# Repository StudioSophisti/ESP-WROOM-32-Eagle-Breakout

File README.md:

# ESP-WROOM-32-Eagle-Breakout
A breadboard compatible Eagle breakout board for Espressif's ESP32 module ESP-WROOM-32. The ESP32 is a powerful and low-cost Wifi/Bluetooth chip that enables great Internet-Of-Things applications. Studio Sophisti is using this chip in several projects, including a work-in-progress redesign of Ping (http://www.studiosophisti.nl/ping)

The ESP-WROOM-32 can be purchased directly from Espressif or from a distributor like Adafruit: https://www.adafruit.com/product/3320

The board contains reverse-voltage protections, 2 buttons (1 for reset and 1 for activating programming mode), and a diode on the RX line so the IC is 5V serial port compatible.

Power it from a 3.0-3.3V power source.

The design has been tested and works.

### Partlist

- 2 SPST switches: Farnell 2468741
- 2 10k resistors: Farnell 2130939
- 1 10uF capacitor: Farnell 2494230
- 1 1N4148 diode: Farnell 1466524
- 1 2N2007E mosfet: Farnell 2317616

### PCB Preview

Generated with GerberTools from ThisIsNotRocketScience (https://github.com/ThisIsNotRocketScience/GerberTools), thanks Stijn!

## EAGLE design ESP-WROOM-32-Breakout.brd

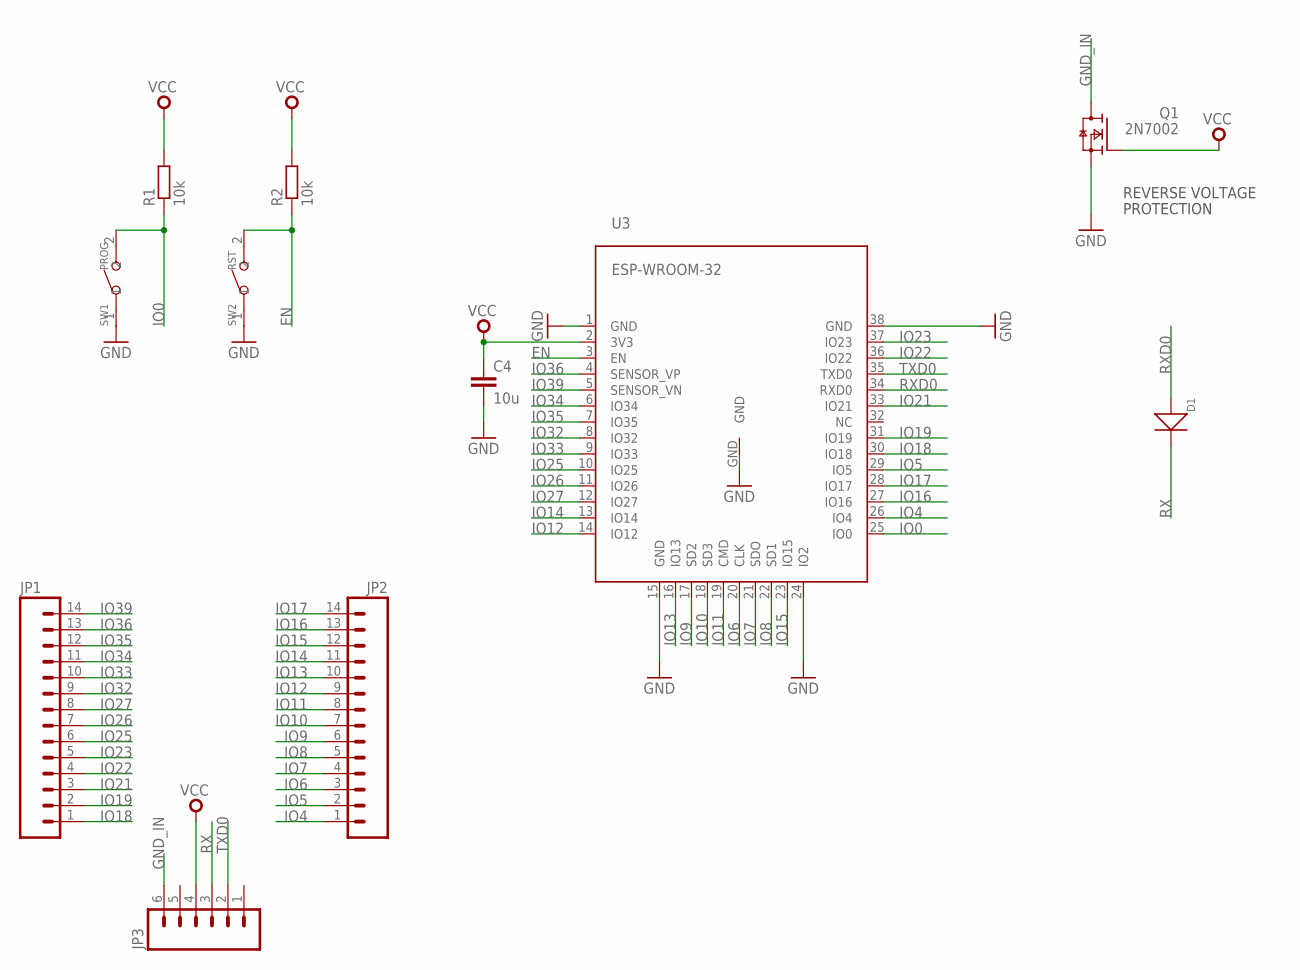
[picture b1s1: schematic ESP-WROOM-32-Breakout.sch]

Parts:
C4: 10u; C0603
D1: DIODE'0805'; SOD-323
JP1, JP2: M14; 1X14
JP3: M06SILK_FEMALE_PTH; 1X06
Q1: 2N7002; SOT23
R1, R2: 10k; R0603
SW1: PROG; SW2-4.0-6.0X3.0X2.5MM
SW2: RST; SW2-4.0-6.0X3.0X2.5MM
U3: ESP-WROOM-32

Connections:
EN: R2.1, SW2.2, U3.3 (EN)
GND: C4.2, Q1.2 (S), SW1.1, SW2.1, U3.1 (GND), U3.15 (GND), U3.24 (IO2), U3.38 (GND), U3.GND
GND_IN: JP3.6, Q1.3 (D)
IO0: R1.1, SW1.2, U3.25 (IO0)
IO4: JP2.1, U3.26 (IO4)
IO5: JP2.2, U3.29 (IO5)
IO6: JP2.3, U3.20 (CLK)
IO7: JP2.4, U3.21 (SDO)
IO8: JP2.5, U3.22 (SD1)
IO9: JP2.6, U3.17 (SD2)
IO10: JP2.7, U3.18 (SD3)
IO11: JP2.8, U3.19 (CMD)
IO12: JP2.9, U3.14 (IO12)
IO13: JP2.10, U3.16 (IO13)
IO14: JP2.11, U3.13 (IO14)
IO15: JP2.12, U3.23 (IO15)
IO16: JP2.13, U3.27 (IO16)
IO17: JP2.14, U3.28 (IO17)
IO18: JP1.1, U3.30 (IO18)
IO19: JP1.2, U3.31 (IO19)
IO21: JP1.3, U3.33 (IO21)
IO22: JP1.4, U3.36 (IO22)
IO23: JP1.5, U3.37 (IO23)
IO25: JP1.6, U3.10 (IO25)
IO26: JP1.7, U3.11 (IO26)
IO27: JP1.8, U3.12 (IO27)
IO32: JP1.9, U3.8 (IO32)
IO33: JP1.10, U3.9 (IO33)
IO34: JP1.11, U3.6 (IO34)
IO35: JP1.12, U3.7 (IO35)
IO36: JP1.13, U3.4 (SENSOR_VP)
IO39: JP1.14, U3.5 (SENSOR_VN)
RX: D1.-, JP3.3
RXD0: D1.+, U3.34 (RXD0)
TXD0: JP3.2, U3.35 (TXD0)
VCC: C4.1, JP3.4, Q1.1 (G), R1.2, R2.2, U3.2 (3V3)

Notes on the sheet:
REVERSE VOLTAGE
PROTECTION

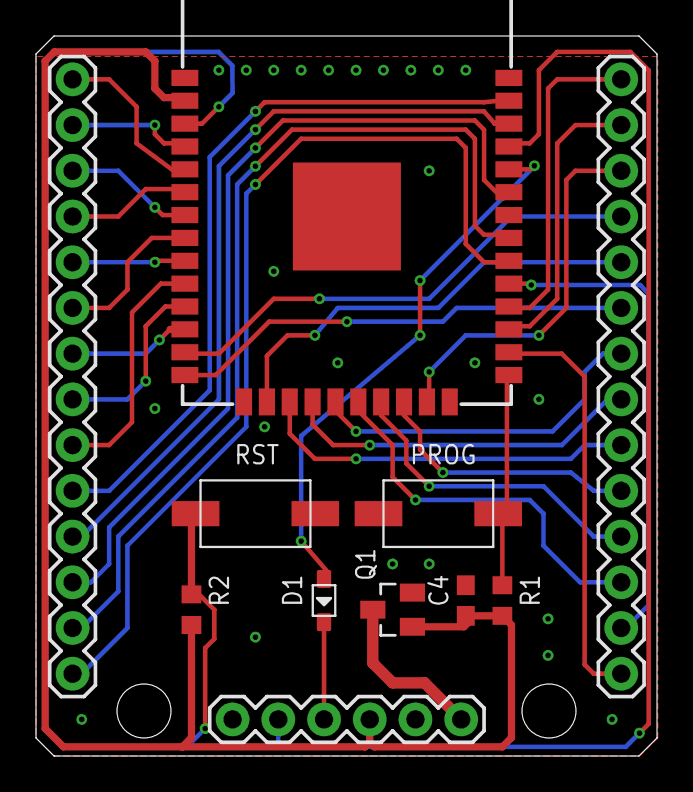
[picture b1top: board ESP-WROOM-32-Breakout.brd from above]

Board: 2 copper layers, 34.5 x 40.0 mm, 11 parts (0 on the bottom side), 36 nets.

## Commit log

2016-11-26 first version of breakout board
2016-11-27 smaller header pads reduced board size added mounting holes stitching via’s at antenna
2016-11-27 improved silks
2016-11-27 added gerbers
2016-11-27 added preview images
2016-11-27 added reverse-voltage protection
2016-11-27 changed diode package to SOD-323
2017-03-23 Add Keepout and Restrict layers under antenna trace, to remove ground plane.
2018-06-06 IO34 and IO35 are only useable as inputs (see page 7 of https://cdn.sparkfun.com/datasheets/IoT/esp32_datasheet_en.pdf); added note in symbol therefore

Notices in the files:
parts and their libraries:
SparkFun-Connectors: Licensing: Creative Commons ShareAlike 4.0 International - https://creativecommons.org/licenses/by-sa/4.0
